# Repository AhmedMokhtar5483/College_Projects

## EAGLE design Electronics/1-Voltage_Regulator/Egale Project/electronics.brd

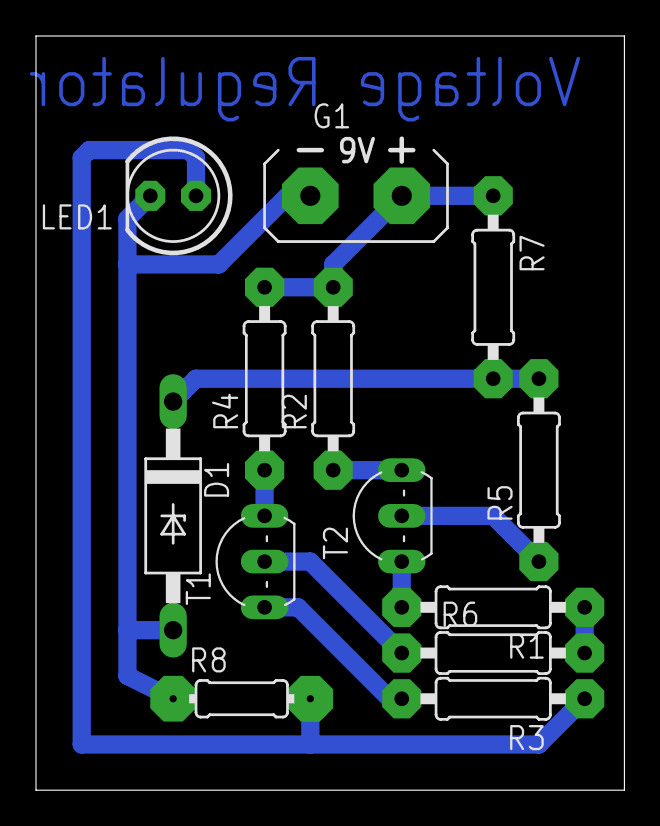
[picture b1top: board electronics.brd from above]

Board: 2 copper layers, 32.7 x 41.9 mm, 13 parts (0 on the bottom side), 11 nets.

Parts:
D1: F126Z12
G1: AB9V
LED1: LED5MM
R1, R2, R3, R4, R5, R6: 1; 0207/10
R7: 1K; 0207/10
R8: 2K; 0204/7
T1, T2: 2N2222; TO92-EBC-OVAL

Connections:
unnamed: R2.1, T2.C
unnamed: R4.1, T1.C
unnamed: R6.1, T1.B
unnamed: R1.1, R6.2
unnamed: R1.2, T2.E
unnamed: R5.1, T2.B
unnamed: D1.C, R5.2, R7.2
unnamed: G1.+, R2.2, R4.2, R7.1
unnamed: R3.2, T1.E
unnamed: LED1.A, R3.1, R8.2
unnamed: D1.A, G1.-, LED1.K, R8.1

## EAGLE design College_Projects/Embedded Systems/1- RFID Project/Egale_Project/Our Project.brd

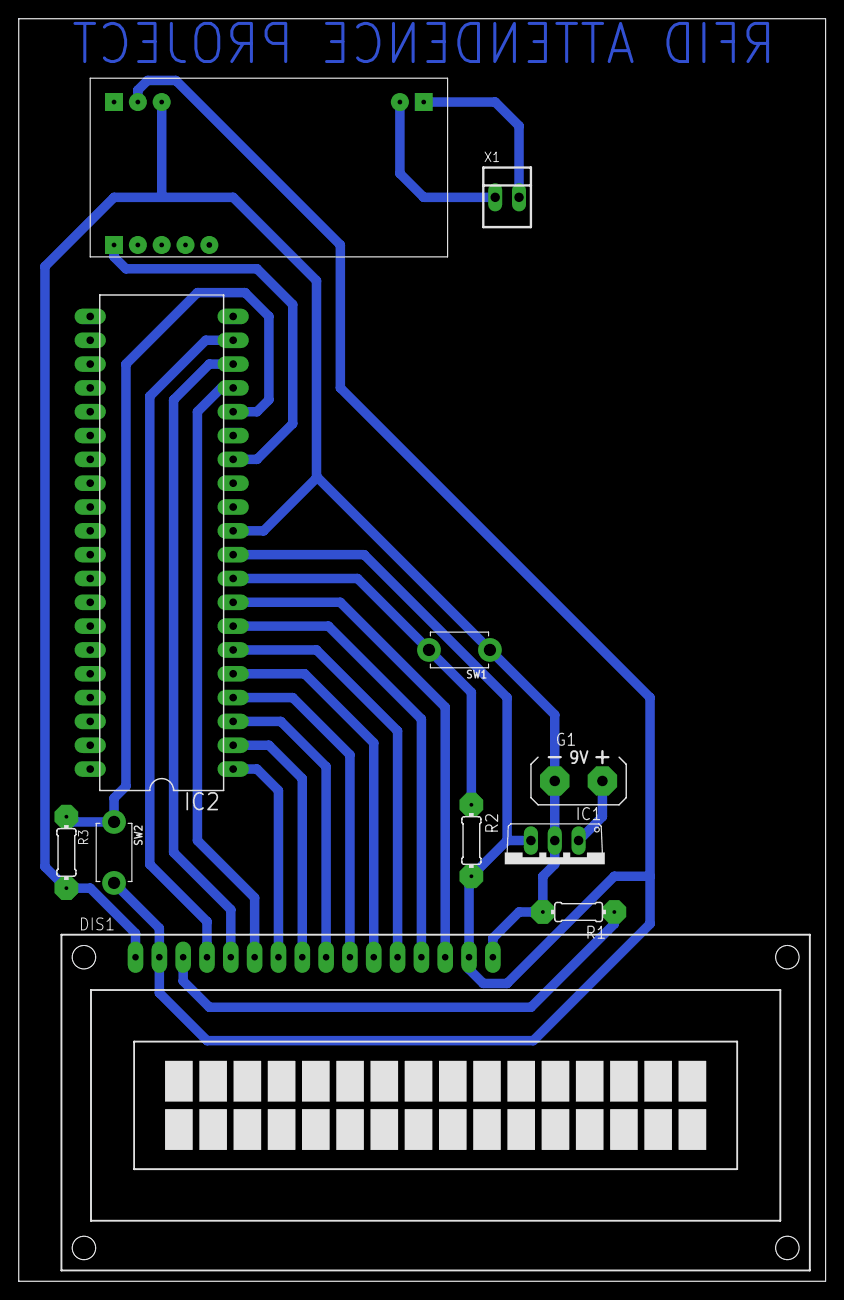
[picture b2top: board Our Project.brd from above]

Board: 2 copper layers, 86.0 x 134.6 mm, 11 parts (0 on the bottom side), 20 nets.

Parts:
DIS1: TUXGR_16X2_R2
G1: AB9V
IC1: 7805TV; TO220V
IC2: MEGA32-P; DIL40
R1, R2, R3: 0204/7
RFID.MOKH1: KIT.RFID.RDM6300
SW1, SW2: TACT_PANA-EVQ
X1: 22-23-2021

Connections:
unnamed: DIS1.14, IC2.8
unnamed: DIS1.13, IC2.7
unnamed: DIS1.11, IC2.5
unnamed: DIS1.12, IC2.6
unnamed: DIS1.4, IC2.19
unnamed: DIS1.6, IC2.17
unnamed: DIS1.3, R1.1
unnamed: IC2.14, RFID.MOKH1.DATA0
unnamed: DIS1.2, DIS1.15, IC1.3, IC2.10, R2.2, RFID.MOKH1.+5(DC)., SW2.P$2
unnamed: DIS1.1, DIS1.16, G1.-, IC1.2, IC2.11, R1.2, R3.2, RFID.MOKH1.GND., SW1.P$1
unnamed: IC2.9, R2.1, SW1.P$2
unnamed: IC2.16, R3.1, SW2.P$1
unnamed: G1.+, IC1.1
unnamed: DIS1.10, IC2.4
unnamed: DIS1.9, IC2.3
unnamed: DIS1.8, IC2.2
unnamed: DIS1.7, IC2.1
unnamed: RFID.MOKH1.ANT1, X1.2
unnamed: RFID.MOKH1.ANT2, X1.1
unnamed: DIS1.5, IC2.18

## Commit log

2022-11-07 Add 1st year projects.
2022-11-09 Edit files name.
2022-11-10 Add 2nd year Projects.
2022-11-13 Add 3rd year Projects #1.
2022-11-13 card_design_1
2022-11-25 Add 3rd year Projects.
2022-11-25 Add 4th year Projects.
